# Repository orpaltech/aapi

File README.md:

ORPAL AA-PI
==============

Antenna analyzer project for portable Linux-based devices. 
The current hardware implementation is based on BananaPi M2-Magic SBC (Allwinner R16).

Version 4.3

Based on the Yuri Kuchura's EU1KY_AA_V3 https://github.com/EU1KY/eu1ky_aa_v3

Build
==============

The build process depends on the platform you have chosen. Currently the AA-PI software is managed by repository https://github.com/orpaltech/armlinux.

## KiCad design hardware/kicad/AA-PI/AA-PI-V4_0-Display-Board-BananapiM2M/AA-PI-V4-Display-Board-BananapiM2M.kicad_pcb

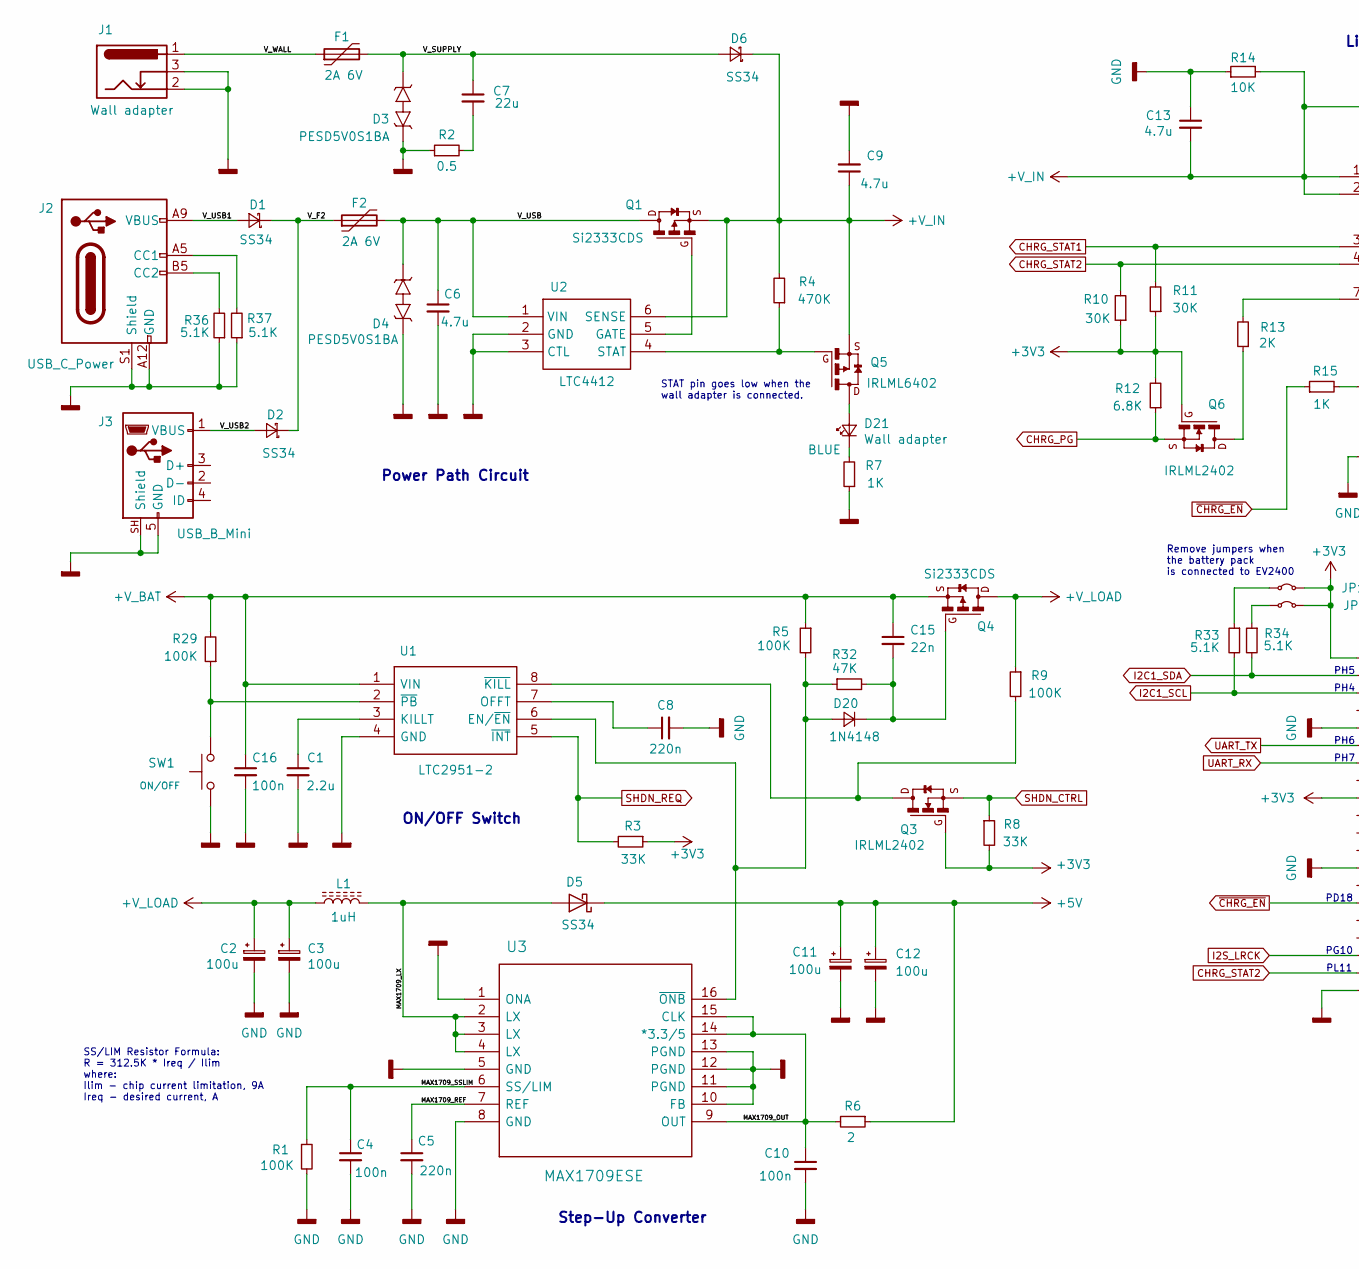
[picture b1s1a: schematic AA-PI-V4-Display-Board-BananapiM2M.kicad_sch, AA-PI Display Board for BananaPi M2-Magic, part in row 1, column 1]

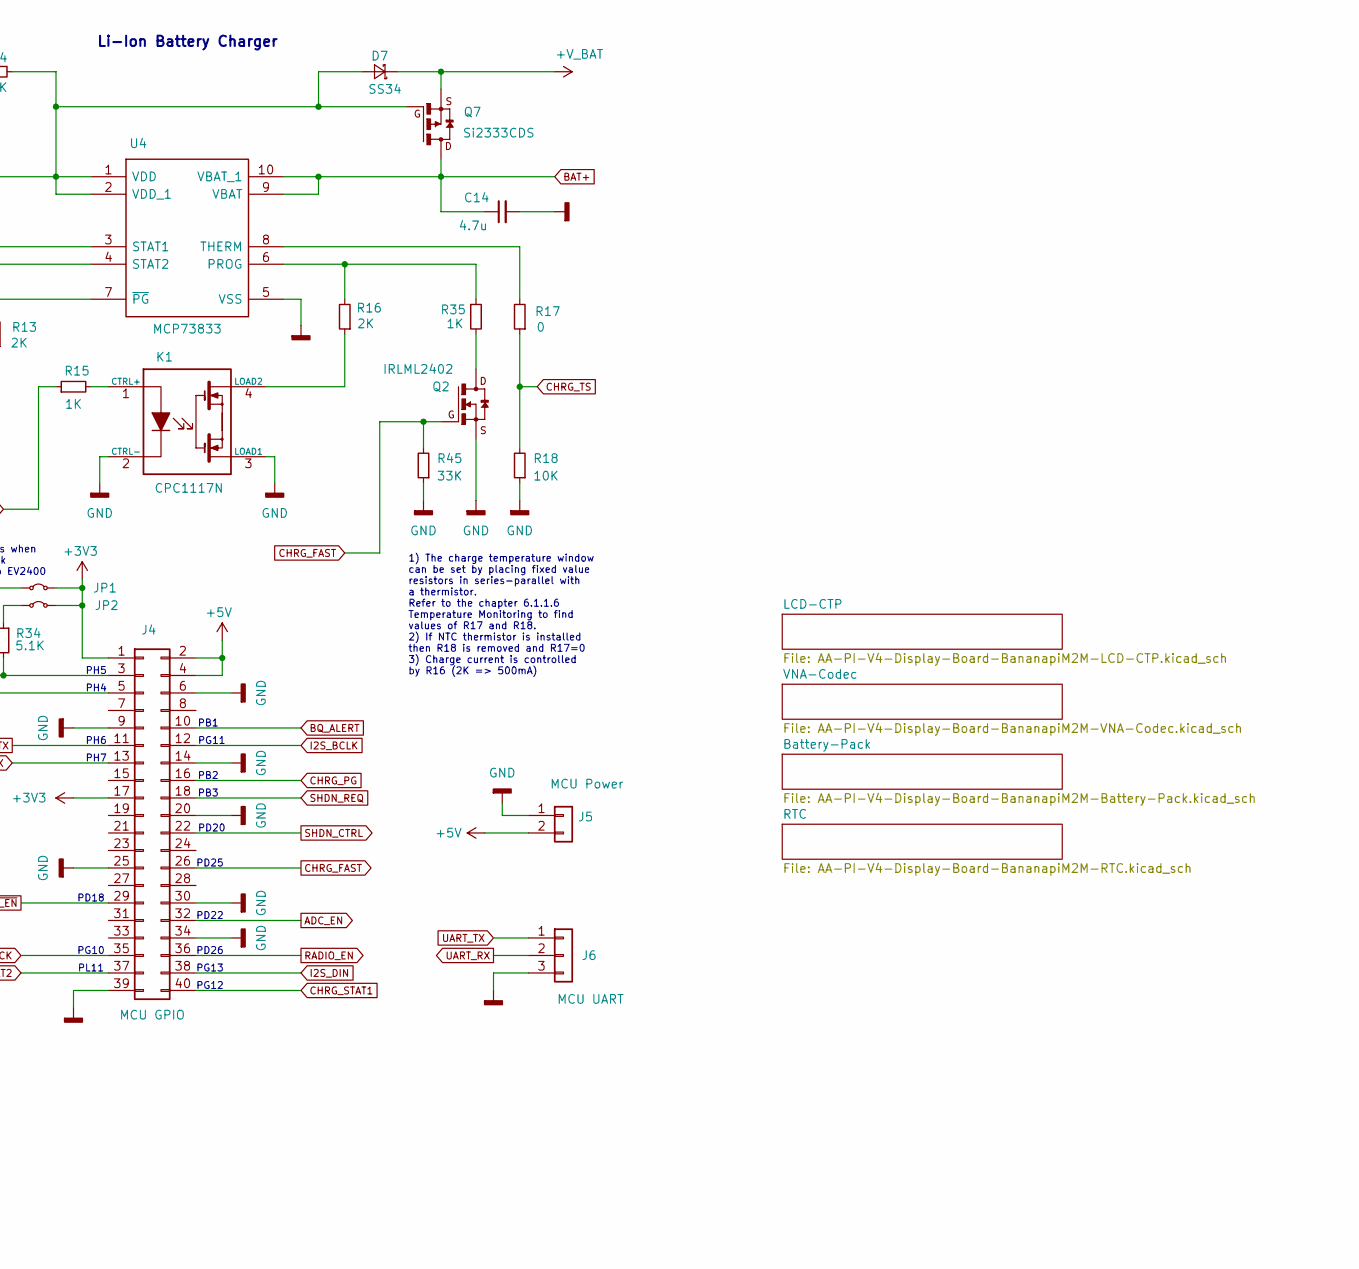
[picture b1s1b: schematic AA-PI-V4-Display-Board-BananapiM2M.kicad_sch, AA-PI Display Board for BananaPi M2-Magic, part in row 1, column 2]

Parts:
C1: 2.2u; C_0603_1608Metric
C2, C3, C11, C12: 100u; CP_EIA-7343-31_Kemet-D
C4, C10: 100n; C_1206_3216Metric
C5: 220n; C_1206_3216Metric
C6, C9, C13, C14: 4.7u; C_0805_2012Metric
C7: 22u; C_1206_3216Metric
C8: 220n; C_0603_1608Metric
C15: 22n; C_0603_1608Metric
C16: 100n; C_0603_1608Metric
D1, D2, D5, D6, D7: SS34; D_SMA
D3, D4: PESD5V0S1BA; D_SOD-323_HandSoldering
D20: 1N4148; D_SOD-323_HandSoldering
D21: Wall adapter; LED_0805_2012Metric_Pad1.15x1.40mm_HandSolder
F1, F2: 2A 6V; Fuse_1206_3216Metric_Pad1.42x1.75mm_HandSolder
J1: Wall adapter; DC-050-SMD-Power-Jack
J2: USB_C_Power; USB_C_Receptacle_GCT_USB4125-xx-x_6P_TopMnt_Horizontal
J3: USB_B_Mini; USB_Mini-B_Lumberg_2486_01_Horizontal
J4: MCU GPIO; PinSocket_2x20_P2.54mm_Vertical_SMD
J5: MCU Power; JST_PH_B2B-PH-SM4-TB_1x02-1MP_P2.00mm_Vertical
J6: MCU UART; PinHeader_1x03_P2.54mm_Vertical_SMD_Pin1Left
JP1, JP2: Jumper_2_Small_Bridged; PinHeader_2x01_P2.00mm_Vertical_SMD
K1: CPC1117N; SOP254P610X218-4N; Manufacturer_Part_Number CPC1117N
L1: 1uH; COILCRAFT_DO3316P102MLB
Q1, Q4, Q7: Si2333CDS; SOT-23
Q2, Q3, Q6: IRLML2402; SOT-23
Q5: IRLML6402; SOT-23
R1: 100K; R_1206_3216Metric
R2: 0.5; R_0805_2012Metric
R3, R8, R45: 33K; R_0603_1608Metric
R4: 470K; R_0805_2012Metric
R5, R9, R29: 100K; R_0603_1608Metric
R6: 2; R_1206_3216Metric
R7: 1K; R_0805_2012Metric
R10, R11: 30K; R_0603_1608Metric
R12: 6.8K; R_0603_1608Metric
R13, R16: 2K; R_0603_1608Metric
R14: 10K; R_0805_2012Metric
R15, R35: 1K; R_0603_1608Metric
R17: 0; R_0603_1608Metric
R18: 10K; R_0603_1608Metric
R32: 47K; R_0603_1608Metric
R33, R34: 5.1K; R_0603_1608Metric
R36, R37: 5.1K; R_0805_2012Metric
SW1: ON/OFF; SW_SPST_CK_RS282G05A3
U1: LTC2951-2; SOT65P280X100-8N; Manufacturer_Part_Number LTC2951CTS8-1#TRMPBF
U2: LTC4412; SOT95P280X100-6N; Manufacturer_Part_Number LTC4412ES6#TRMPBF
U3: MAX1709ESE; SOIC-16_3.9x9.9mm_P1.27mm
U4: MCP73833; SOP50P490X110-10N; Manufacturer_Part_Number MCP73833-FCI/UN

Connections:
+3V3: J4.1, J4.17, JP1.2 (B), JP2.2 (B), Q3.1 (G), Q6.1 (G), R3.1, R8.2, R10.1, R11.1, R12.2; also elsewhere on the board
+5V: C11.1, C12.1, D5.1 (K), J4.2, J4.4, J5.2, R6.1; also elsewhere on the board
+V_BAT: C15.1, C16.1, D7.1 (K), Q4.2 (S), Q7.2 (S), R5.1, R29.2, U1.1 (VIN)
+V_IN: C9.1, C13.2, D6.1 (K), D7.2 (A), Q1.2 (S), Q5.2 (S), Q7.1 (G), R4.2, R14.2, U2.6 (SENSE), U4.1 (VDD), U4.2 (VDD_1)
+V_LOAD: C2.1, C3.1, L1.1, Q4.3 (D), R9.1
/MAX1709_LX: D5.2 (A), L1.2, U3.2 (LX), U3.3 (LX), U3.4 (LX)
/MAX1709_OUT: C10.1, R6.2, U3.9 (OUT), U3.14 (*3.3/5), U3.15 (CLK)
/MAX1709_REF: C5.1, U3.7 (REF)
/MAX1709_SSLIM: C4.1, R1.1, U3.6 (SS/LIM)
/V_F2: D1.1 (K), D2.1 (K), F2.1
/V_SUPPLY: C7.1, D3.2, D6.2 (A), F1.2
/V_USB: C6.1, D4.2, F2.2, Q1.3 (D), U2.1 (VIN)
/V_USB1: D1.2 (A), J2.A9 (VBUS), J2.B9 (VBUS)
/V_USB2: D2.2 (A), J3.1 (VBUS)
/V_WALL: F1.1, J1.1
ADC_EN: J4.32; also elsewhere on the board
BAT+: C14.1, Q7.3 (D), U4.9 (VBAT), U4.10 (VBAT_1); also elsewhere on the board
BQ_ALERT: J4.10; also elsewhere on the board
CHRG_FAST: J4.26, Q2.1 (G), R45.2
CHRG_PG: J4.16, Q6.2 (S), R12.1
CHRG_STAT1: J4.40, R11.2, U4.3 (STAT1)
CHRG_STAT2: J4.37, R10.2, U4.4 (STAT2)
CHRG_TS: R17.1, R18.2; also elsewhere on the board
GND: C1.2, C2.2, C3.2, C4.2, C5.2, C6.2, C8.2, C9.2, C10.2, C11.2, C12.2, C13.1, C14.2, C16.2, D3.1, D4.1, J1.2, J1.3, J2.A12 (GND), J2.B12 (GND), J2.S1 (Shield), J3.5 (GND), J3.SH (Shield), J4.6, J4.9, J4.14, J4.20, J4.25, J4.30, J4.34, J4.39, J5.1, J6.3, K1.2 (CTRL-), K1.3 (LOAD1), Q2.2 (S), R1.2, R2.1, R7.1, R14.1, R18.1, R36.1, R37.1, R45.1, SW1.1, U1.4 (GND), U2.2 (GND), U2.3 (CTL), U3.1 (ONA), U3.5 (GND), U3.8 (GND), U3.10 (FB), U3.11 (PGND), U3.12 (PGND), U3.13 (PGND), U4.5 (VSS); also elsewhere on the board
I2C1_SCL: J4.5, R33.2; also elsewhere on the board
I2C1_SDA: J4.3, R34.2; also elsewhere on the board
I2S_BCLK: J4.12; also elsewhere on the board
I2S_DIN: J4.38; also elsewhere on the board
I2S_LRCK: J4.35; also elsewhere on the board
unnamed: C7.2, R2.2
unnamed: D20.2 (A), R5.2, R32.1, U1.6 (EN/~EN), U3.16 (~ONB)
unnamed: C15.2, D20.1 (K), Q4.1 (G), R32.2
unnamed: D21.2 (A), Q5.3 (D)
unnamed: D21.1 (K), R7.2
unnamed: J2.A5 (CC1), R37.2
unnamed: J2.B5 (CC2), R36.2
unnamed: JP1.1 (A), R33.1
unnamed: JP2.1 (A), R34.1
unnamed: K1.1 (CTRL+), R15.2
unnamed: K1.4 (LOAD2), R16.1
unnamed: Q1.1 (G), U2.5 (GATE)
unnamed: Q2.3 (D), R35.2
unnamed: Q3.3 (D), R9.2, U1.8 (~KILL)
unnamed: Q5.1 (G), R4.1, U2.4 (STAT)
unnamed: Q6.3 (D), R13.1
unnamed: C1.1, U1.3 (KILLT)
unnamed: C8.1, U1.7 (OFFT)
unnamed: R29.1, SW1.2, U1.2 (~PB)
unnamed: R16.2, R35.1, U4.6 (PROG)
unnamed: R17.2, U4.8 (THERM)
unnamed: R13.2, U4.7 (~PG)
RADIO_EN: J4.36; also elsewhere on the board
SHDN_CTRL: J4.22, Q3.2 (S), R8.1
SHDN_REQ: J4.18, R3.2, U1.5 (~INT)
UART_RX: J4.13, J6.2
UART_TX: J4.11, J6.1
~CHRG_EN: J4.29, R15.1

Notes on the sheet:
PH4
PD26
SS/LIM Resistor Formula: R = 312.5K * Ireq / Ilim where: Ilim - chip current limitation, 9A Ireq - desired current, A
STAT pin goes low when the wall adapter is connected.
PD20
PG12
PG10
PB1
PB3
Power Path Circuit
1) The charge temperature window can be set by placing fixed value resistors in series-parallel with a thermistor. Refer to the chapter 6.1.1.6 Temperature Monitoring to find values of R17 and R18. 2) If NTC thermistor is installed then R18 is removed and R17=0 3) Charge current is controlled by R1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
PG11
Step-Up Converter
PH6
ON/OFF Switch
PH7
PB2
Remove jumpers when the battery pack is connected to EV2400
PD18
PG13
PD25
PH5
PD22
Li-Ion Battery Charger
PL11

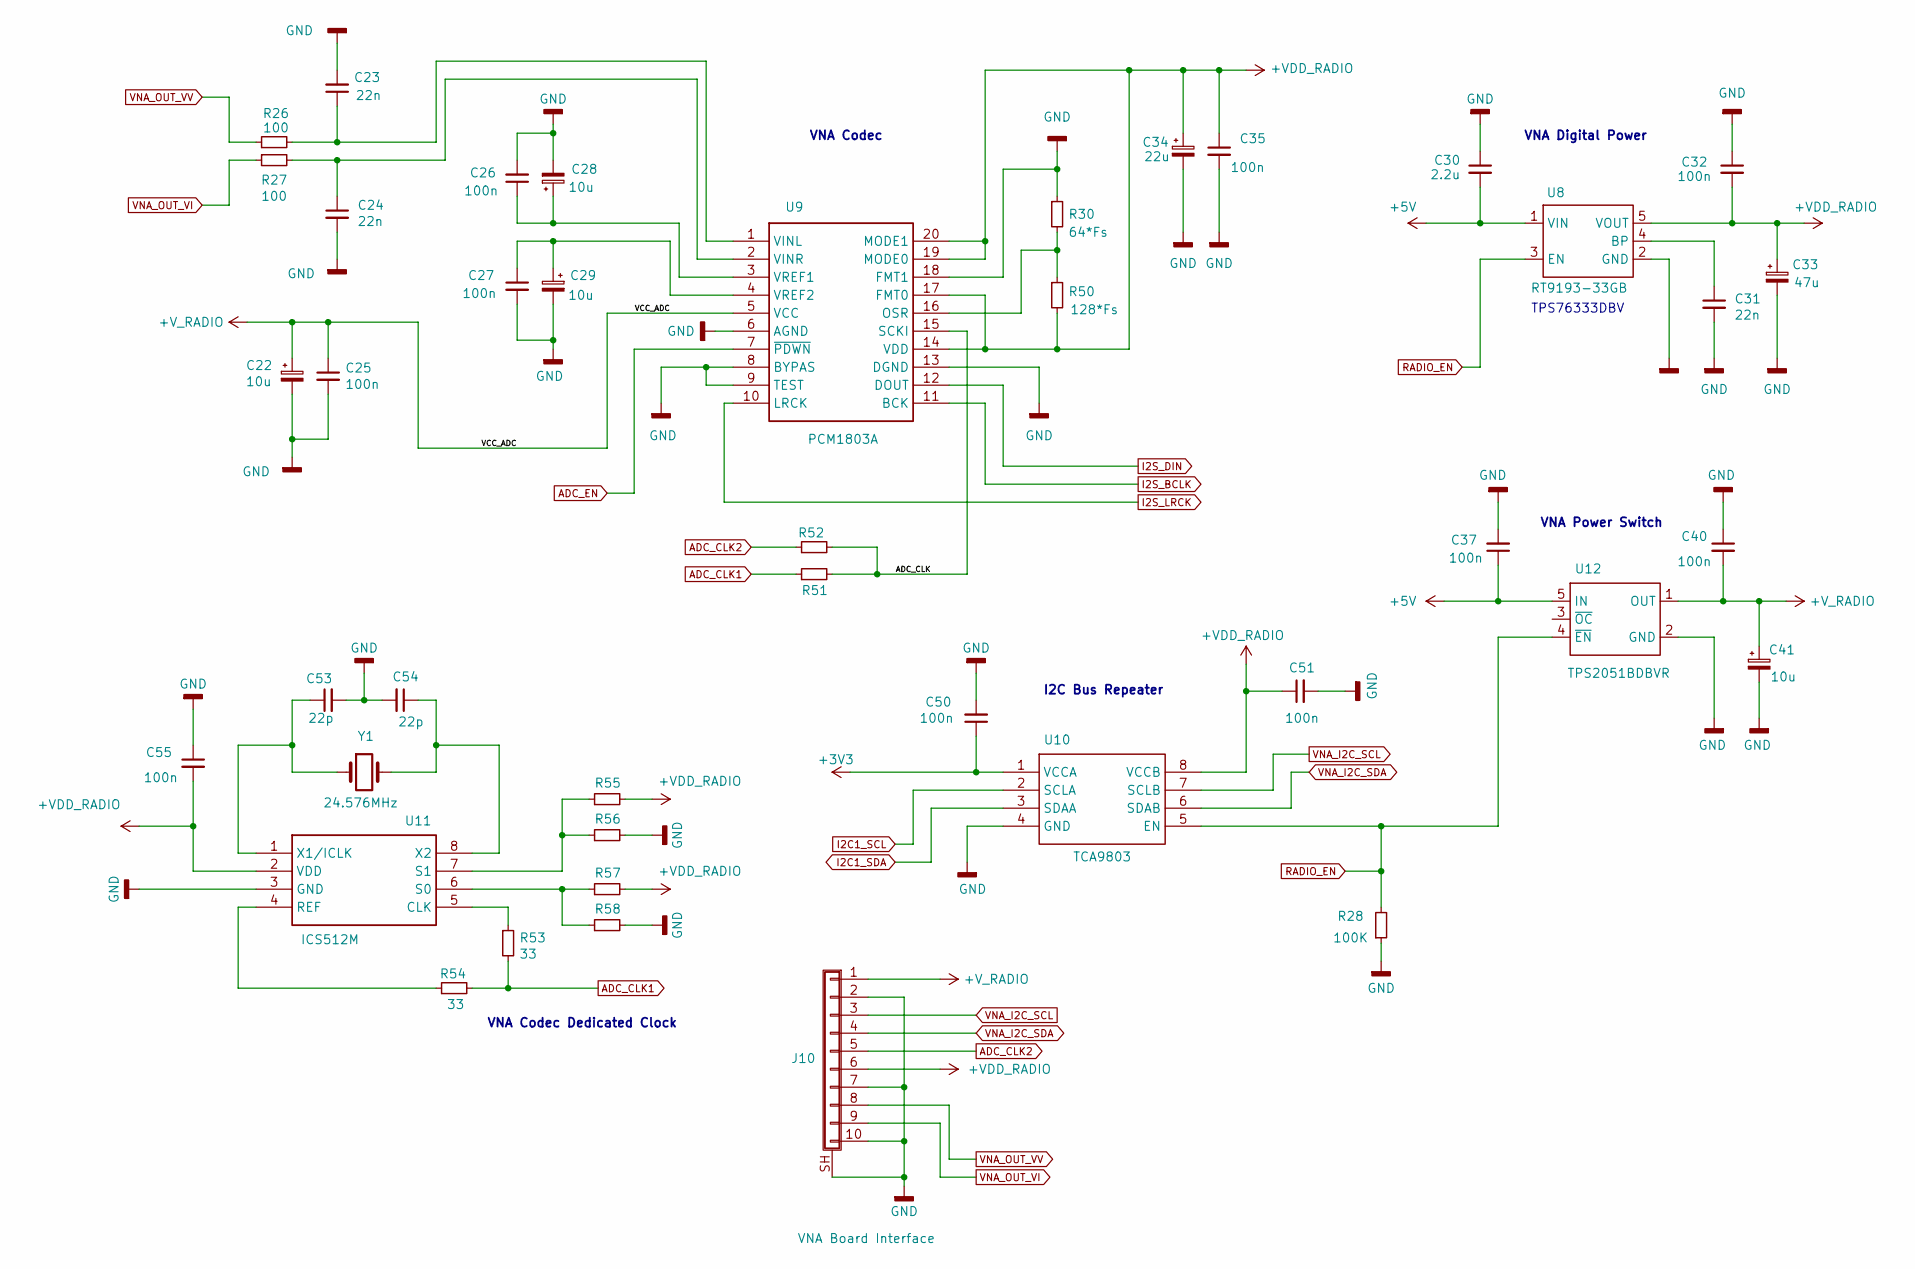
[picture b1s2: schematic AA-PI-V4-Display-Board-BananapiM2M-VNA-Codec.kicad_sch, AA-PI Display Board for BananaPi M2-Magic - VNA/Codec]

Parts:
C22, C28, C29: 10u; CP_EIA-3216-18_Kemet-A
C23, C24: 22n; C_0603_1608Metric
C25, C26, C27, C35, C50, C51, C55: 100n; C_0603_1608Metric
C30: 2.2u; C_0805_2012Metric_Pad1.15x1.40mm_HandSolder
C31: 22n; C_0805_2012Metric
C32, C37, C40: 100n; C_0805_2012Metric
C33: 47u; CP_EIA-3528-21_Kemet-B
C34: 22u; CP_EIA-3216-18_Kemet-A
C41: 10u; CP_EIA-3528-21_Kemet-B
C53, C54: 22p; C_0603_1608Metric
J10: VNA Board Interface; 1.25-AB-SMT-10pin-Vertical
R26, R27: 100; R_0603_1608Metric
R28: 100K; R_0603_1608Metric
R30: 64*Fs; R_0603_1608Metric
R50: 128*Fs; R_0603_1608Metric
R51, R52, R55, R56, R57, R58: 0; R_0603_1608Metric
R53, R54: 33; R_0603_1608Metric
U8: RT9193-33GB; SOT94P279X130-5N; Manufacturer_Part_Number RT9193
U9: PCM1803A; SOP65P780X200-20N; Manufacturer_Part_Number PCM1803DBR; Mouser Part Number 595-PCM1803DBR
U10: TCA9803; SOP65P490X110-8N; Manufacturer_Part_Number TCA9802DGKR
U11: ICS512M; SOIC127P600X175-8N; Manufacturer_Part_Number ICS512MILF
U12: TPS2051BDBVR; SOT95P280X145-5N; Manufacturer_Part_Number TPS2051BDBVR
Y1: 24.576MHz; Crystal_SMD_5032-2Pin_5.0x3.2mm

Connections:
+3V3: C50.1, U10.1 (VCCA); also elsewhere on the board
+5V: C30.2, C37.1, U8.1 (VIN), U12.5 (IN); also elsewhere on the board
+VDD_RADIO: C32.2, C33.1, C34.1, C35.1, C51.1, C55.2, J10.6, R50.2, R55.2, R57.2, U8.5 (VOUT), U9.14 (VDD), U9.17 (FMT0), U9.19 (MODE0), U9.20 (MODE1), U10.8 (VCCB), U11.2 (VDD)
+V_RADIO: C22.1, C25.1, C40.2, C41.1, J10.1, U9.5 (VCC), U12.1 (OUT)
/VNA-Codec/ADC_CLK: R51.2, R52.2, U9.15 (SCKI)
ADC_CLK1: R51.1, R53.2, R54.2
ADC_CLK2: J10.5, R52.1
ADC_EN: U9.7 (~PDWN); also elsewhere on the board
GND: C22.2, C23.2, C24.2, C25.2, C26.2, C27.2, C28.2, C29.2, C30.1, C31.2, C32.1, C33.2, C34.2, C35.2, C37.2, C40.1, C41.2, C50.2, C51.2, C53.2, C54.2, C55.1, J10.2, J10.7, J10.10, J10.SH (Shield), R28.1, R30.1, R56.2, R58.2, U8.2 (GND), U9.6 (AGND), U9.8 (BYPAS), U9.9 (TEST), U9.13 (DGND), U9.18 (FMT1), U10.4 (GND), U11.3 (GND), U12.2 (GND); also elsewhere on the board
I2C1_SCL: U10.2 (SCLA); also elsewhere on the board
I2C1_SDA: U10.3 (SDAA); also elsewhere on the board
I2S_BCLK: U9.11 (BCK); also elsewhere on the board
I2S_DIN: U9.12 (DOUT); also elsewhere on the board
I2S_LRCK: U9.10 (LRCK); also elsewhere on the board
unnamed: C31.1, U8.4 (BP)
unnamed: R30.2, R50.1, U9.16 (OSR)
unnamed: C23.1, R26.2, U9.1 (VINL)
unnamed: C24.1, R27.2, U9.2 (VINR)
unnamed: C26.1, C28.1, U9.3 (VREF1)
unnamed: C27.1, C29.1, U9.4 (VREF2)
unnamed: R53.1, U11.5 (CLK)
unnamed: R54.1, U11.4 (REF)
unnamed: R57.1, R58.1, U11.6 (S0)
unnamed: R55.1, R56.1, U11.7 (S1)
unnamed: C53.1, U11.1 (X1/ICLK), Y1.1
unnamed: C54.1, U11.8 (X2), Y1.2
RADIO_EN: R28.2, U8.3 (EN), U10.5 (EN), U12.4 (~EN); also elsewhere on the board
VNA_I2C_SCL: J10.3, U10.7 (SCLB)
VNA_I2C_SDA: J10.4, U10.6 (SDAB)
VNA_OUT_VI: J10.9, R27.1
VNA_OUT_VV: J10.8, R26.1

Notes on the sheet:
VNA Power Switch
VNA Codec
VNA Codec Dedicated Clock
I2C Bus Repeater
TPS76333DBV
VNA Digital Power

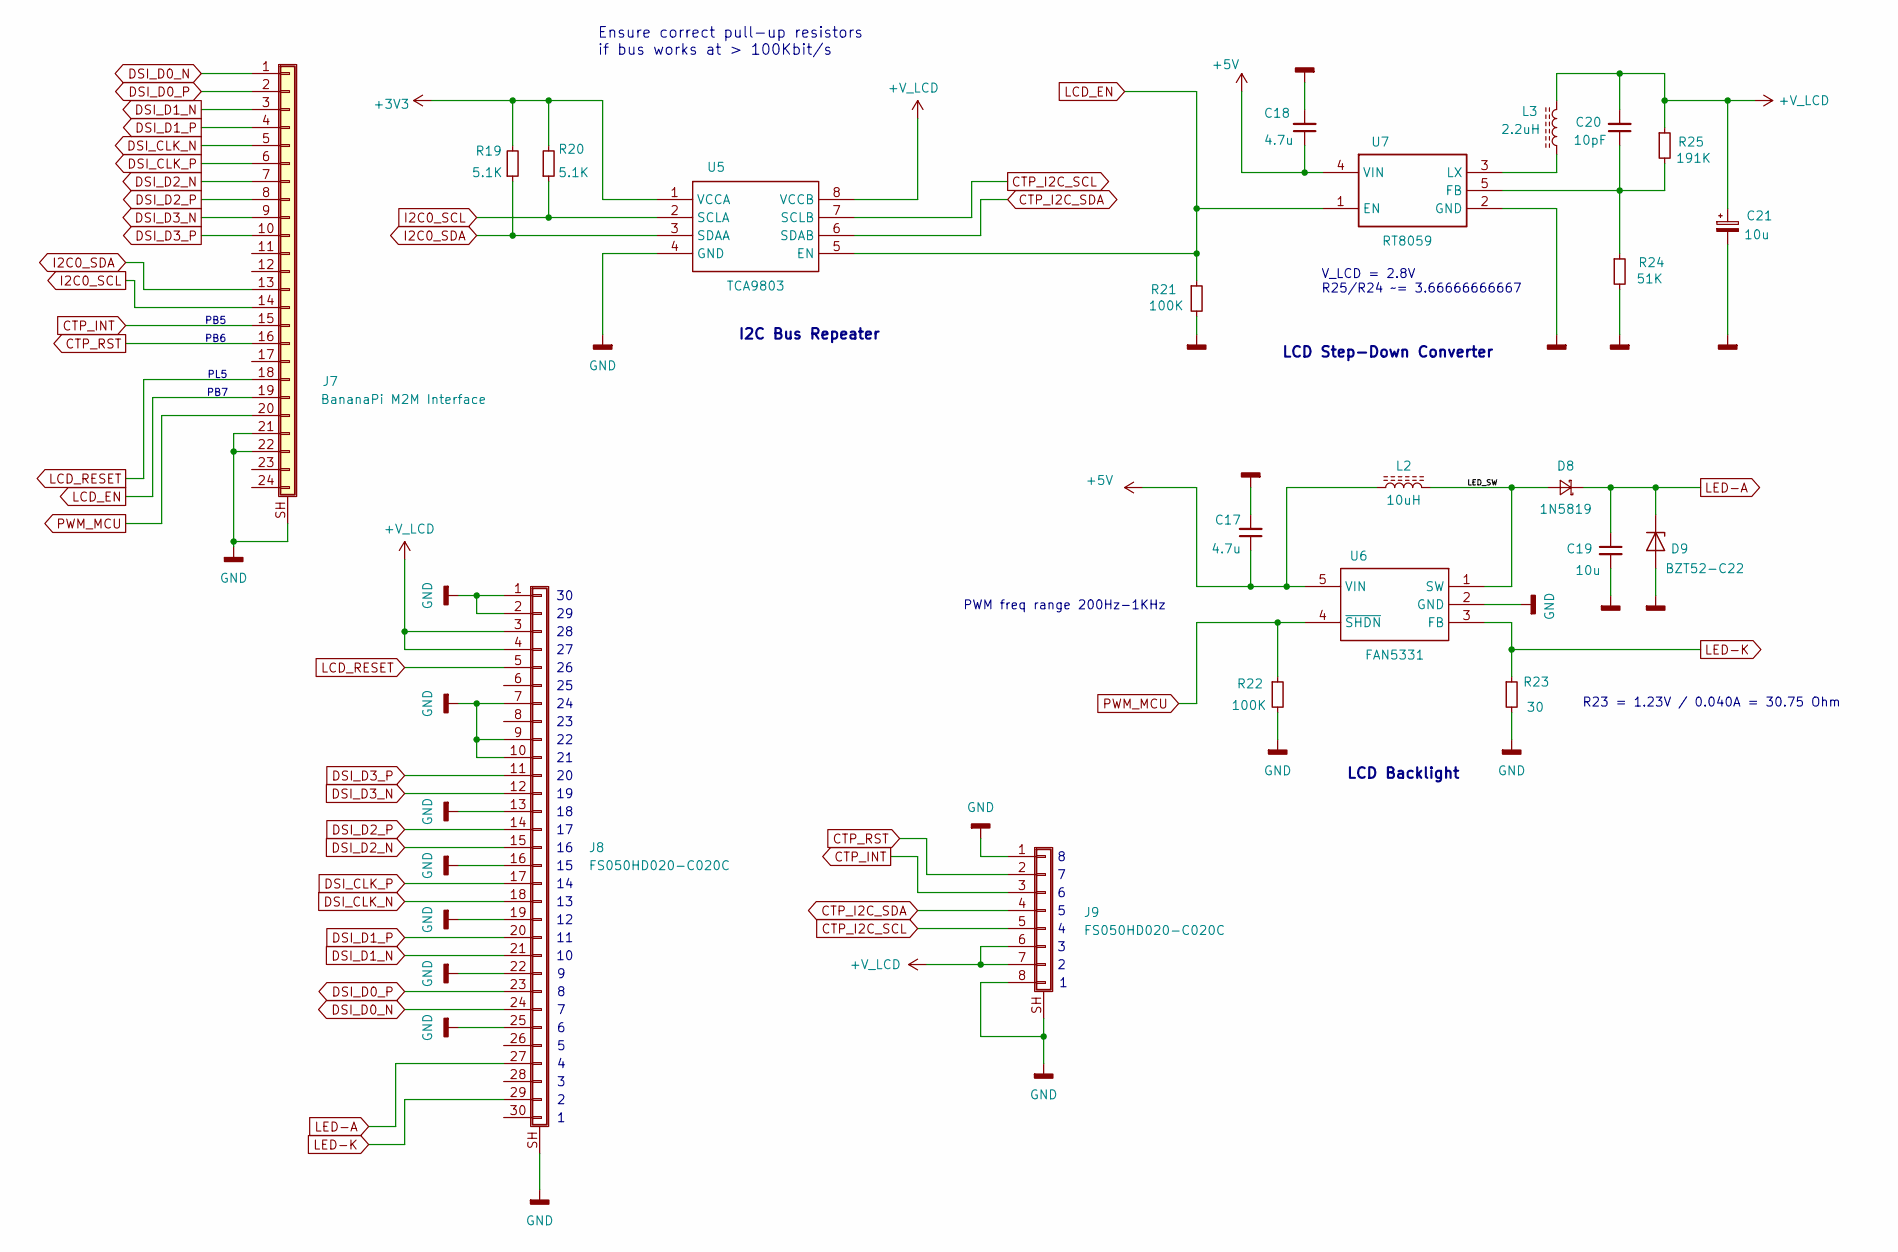
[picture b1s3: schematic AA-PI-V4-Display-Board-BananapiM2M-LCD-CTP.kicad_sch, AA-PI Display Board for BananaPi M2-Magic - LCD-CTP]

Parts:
C17, C18: 4.7u; C_0805_2012Metric
C19: 10u; C_0805_2012Metric
C20: 10pF; C_0805_2012Metric
C21: 10u; CP_EIA-3528-21_Kemet-B
D8: 1N5819; D_SOD-123
D9: BZT52-C22; D_SOD-123
J7: BananaPi M2M Interface; FPC-0.5-1-24P_CLAMSH_BTM
J8: FS050HD020-C020C; FPC-0.5-1-30P_Clamshell_Bottom
J9: FS050HD020-C020C; FPC-0.5-1-8P_Clamshell_Bottom
L2: 10uH; COILCRAFT_XEL5050_HandSolder
L3: 2.2uH; COILCRAFT_XEL5050_HandSolder
R19, R20: 5.1K; R_0603_1608Metric
R21, R22: 100K; R_0603_1608Metric
R23: 30; R_0805_2012Metric
R24: 51K; R_0603_1608Metric
R25: 191K; R_0603_1608Metric
U5: TCA9803; SOP65P490X110-8N; Manufacturer_Part_Number TCA9802DGKR
U6: FAN5331; SOT95P270X145-5N; Manufacturer_Part_Number FAN5333BSX
U7: RT8059; SOT94P280X100-5N; Manufacturer_Part_Number RT8059GJ5; Mouser Part Number 835-RT8059GJ5

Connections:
+3V3: R19.2, R20.2, U5.1 (VCCA); also elsewhere on the board
+5V: C17.1, C18.1, L2.1, U6.5 (VIN), U7.4 (VIN); also elsewhere on the board
+V_LCD: C20.2, C21.1, J8.3, J8.4, J9.6, J9.7, L3.2, R25.1, U5.8 (VCCB)
/LCD-CTP/LED_SW: D8.2 (A), L2.2, U6.1 (SW)
CTP_I2C_SCL: J9.5, U5.7 (SCLB)
CTP_I2C_SDA: J9.4, U5.6 (SDAB)
CTP_INT: J7.15, J9.3
CTP_RST: J7.16, J9.2
DSI_CLK_N: J7.5, J8.18
DSI_CLK_P: J7.6, J8.17
DSI_D0_N: J7.1, J8.24
DSI_D0_P: J7.2, J8.23
DSI_D1_N: J7.3, J8.21
DSI_D1_P: J7.4, J8.20
DSI_D2_N: J7.7, J8.15
DSI_D2_P: J7.8, J8.14
DSI_D3_N: J7.9, J8.12
DSI_D3_P: J7.10, J8.11
GND: C17.2, C18.2, C19.2, C21.2, D9.2 (A), J7.21, J7.22, J7.SH (Shield), J8.1, J8.2, J8.7, J8.9, J8.10, J8.13, J8.16, J8.19, J8.22, J8.25, J8.SH (Shield), J9.1, J9.8, J9.SH (Shield), R21.2, R22.2, R23.2, R24.2, U5.4 (GND), U6.2 (GND), U7.2 (GND); also elsewhere on the board
I2C0_SCL: J7.14, R20.1, U5.2 (SCLA)
I2C0_SDA: J7.13, R19.1, U5.3 (SDAA)
LCD_EN: J7.19, R21.1, U5.5 (EN), U7.1 (EN)
LCD_RESET: J7.18, J8.5
LED-A: C19.1, D8.1 (K), D9.1 (K), J8.27
LED-K: J8.29, R23.1, U6.3 (FB)
unnamed: C20.1, R24.1, R25.2, U7.5 (FB)
unnamed: L3.1, U7.3 (LX)
PWM_MCU: J7.20, R22.1, U6.4 (~SHDN)

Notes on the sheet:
PB7
R23 = 1.23V / 0.040A = 30.75 Ohm
PB6
LCD Step-Down Converter
PWM freq range 200Hz-1KHz
I2C Bus Repeater
LCD Backlight
PB5
PL5
V_LCD = 2.8V R25/R24 ~= 3.66666666667
Ensure correct pull-up resistors if bus works at > 100Kbit/s

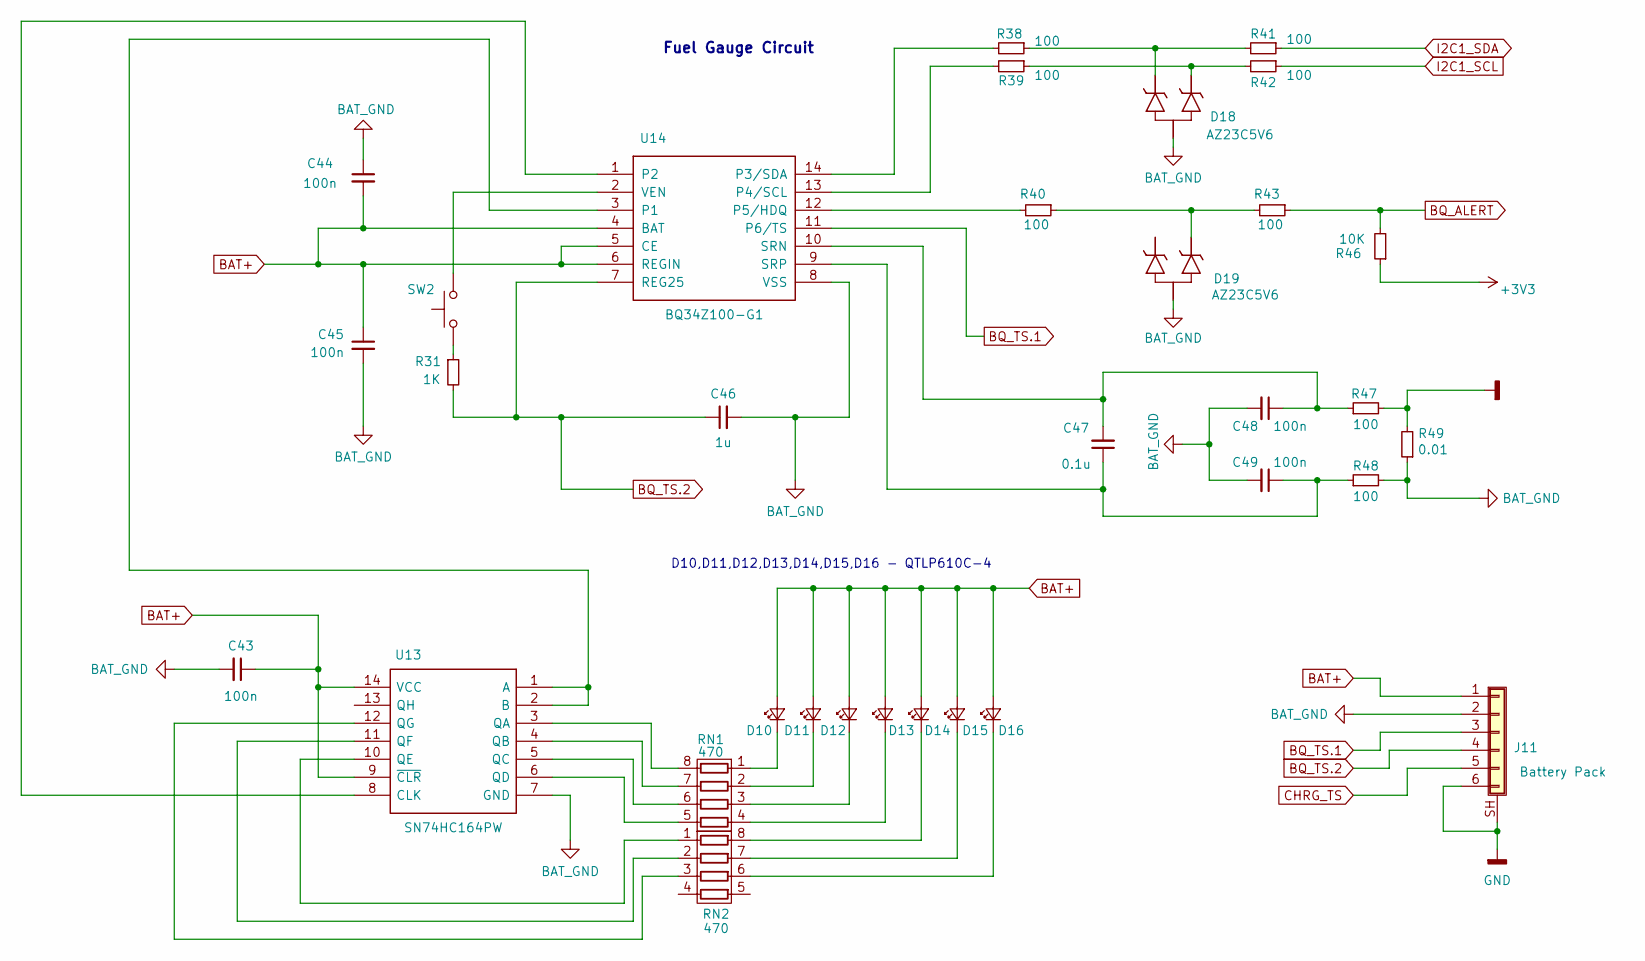
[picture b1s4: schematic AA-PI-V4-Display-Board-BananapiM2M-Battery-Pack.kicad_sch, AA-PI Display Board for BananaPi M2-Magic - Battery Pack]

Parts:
C43, C44, C45, C48, C49: 100n; C_0603_1608Metric
C46: 1u; C_0805_2012Metric_Pad1.15x1.40mm_HandSolder
C47: 0.1u; C_0603_1608Metric
D10, D11, D12, D13, D14, D15, D16: QTLP610C-4; QTLP610C4TR_2; Manufacturer_Part_Number QTLP610C4TR
D18, D19: AZ23C5V6; SOT96P240X110-3N; Manufacturer_Part_Number AZ23C2V7-AZ23C51
J11: Battery Pack; JST_PH_B6B-PH-SM4-TB_1x06-1MP_P2.00mm_Vertical
R31: 1K; R_0603_1608Metric
R38, R39, R40, R41, R42, R43, R47, R48: 100; R_0603_1608Metric
R46: 10K; R_0603_1608Metric
R49: 0.01; R_0805_2012Metric
RN1, RN2: 470; R_Array_Convex_4x0603
SW2: SW_Push; SW_SPST_3X4X2.5_SMD
U13: SN74HC164PW; SOP65P640X120-14N; Manufacturer_Part_Number SN74HC164PW
U14: BQ34Z100-G1; SOP65P640X120-14N; Manufacturer_Part_Number BQ34Z100PWR-G1

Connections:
+3V3: R46.1; also elsewhere on the board
BAT+: C43.1, C44.2, C45.1, D10.2 (A), D11.2 (A), D12.2 (A), D13.2 (A), D14.2 (A), D15.2 (A), D16.2 (A), J11.1, U13.9 (~CLR), U13.14 (VCC), U14.4 (BAT), U14.5 (CE), U14.6 (REGIN); also elsewhere on the board
BAT_GND: C43.2, C44.1, C45.2, C46.2, C48.2, C49.2, D18.3, D19.3, J11.2, R48.2, R49.1, U13.7 (GND), U14.8 (VSS)
BQ_ALERT: R43.1, R46.2; also elsewhere on the board
BQ_TS.1: J11.3, U14.11 (P6/TS)
BQ_TS.2: C46.1, J11.4, R31.2, U14.7 (REG25)
CHRG_TS: J11.5; also elsewhere on the board
GND: J11.6, J11.SH (Shield), R47.2, R49.2; also elsewhere on the board
I2C1_SCL: R42.1; also elsewhere on the board
I2C1_SDA: R41.1; also elsewhere on the board
unnamed: D10.1 (K), RN1.1 (R1.1)
unnamed: D11.1 (K), RN1.2 (R2.1)
unnamed: D12.1 (K), RN1.3 (R3.1)
unnamed: D13.1 (K), RN1.4 (R4.1)
unnamed: D14.1 (K), RN2.8 (R1.2)
unnamed: D15.1 (K), RN2.7 (R2.2)
unnamed: D16.1 (K), RN2.6 (R3.2)
unnamed: D18.1, R39.1, R42.2
unnamed: D18.2, R38.1, R41.2
unnamed: D19.1, R40.1, R43.2
unnamed: R31.1, SW2.1
unnamed: RN1.8 (R1.2), U13.3 (QA)
unnamed: RN1.7 (R2.2), U13.4 (QB)
unnamed: RN1.6 (R3.2), U13.5 (QC)
unnamed: RN1.5 (R4.2), U13.6 (QD)
unnamed: RN2.1 (R1.1), U13.10 (QE)
unnamed: RN2.2 (R2.1), U13.11 (QF)
unnamed: RN2.3 (R3.1), U13.12 (QG)
unnamed: U13.1 (A), U13.2 (B), U14.3 (P1)
unnamed: U13.8 (CLK), U14.1 (P2)
unnamed: R38.2, U14.14 (P3/SDA)
unnamed: R39.2, U14.13 (P4/SCL)
unnamed: R40.2, U14.12 (P5/HDQ)
unnamed: C47.2, C48.1, R47.1, U14.10 (SRN)
unnamed: C47.1, C49.1, R48.1, U14.9 (SRP)
unnamed: SW2.2, U14.2 (VEN)

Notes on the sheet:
D10,D11,D12,D13,D14,D15,D16 - QTLP610C-4
Fuel Gauge Circuit

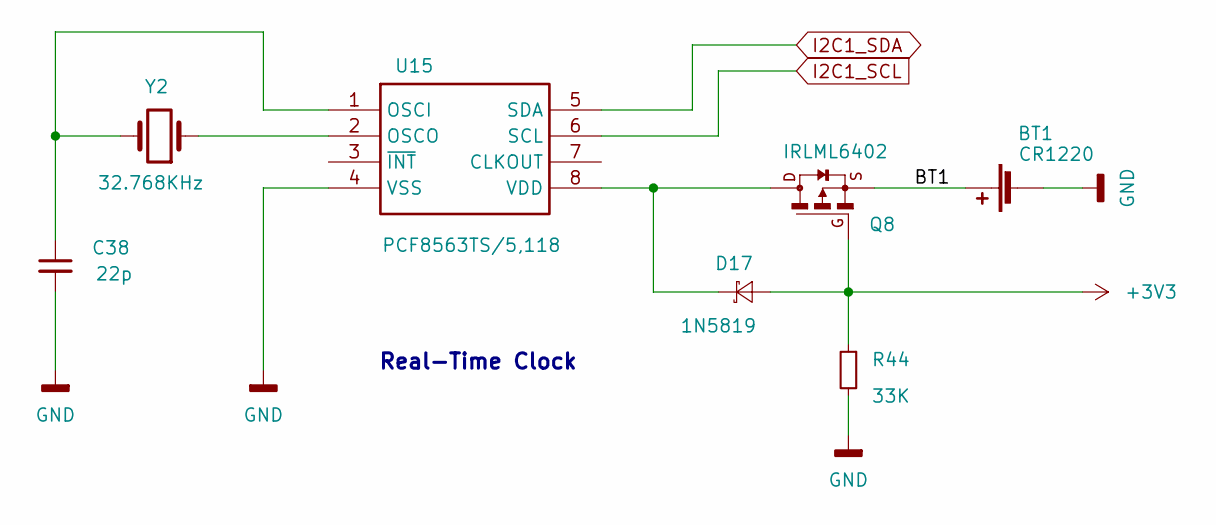
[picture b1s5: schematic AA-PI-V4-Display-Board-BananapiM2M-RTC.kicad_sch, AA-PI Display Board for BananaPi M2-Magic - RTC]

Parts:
BT1: CR1220; CR1220-2
C38: 22p; C_0603_1608Metric
D17: 1N5819; D_SOD-323_HandSoldering
Q8: IRLML6402; SOT-23
R44: 33K; R_0603_1608Metric
U15: PCF8563TS/5,118; SOT65P490X110-8N; Manufacturer_Part_Number PCF8563TS/5,118; Mouser Part Number 771-PCF8563TS/5118
Y2: 32.768KHz; Crystal_SMD_3215-2Pin_3.2x1.5mm

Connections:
+3V3: D17.2 (A), Q8.1 (G), R44.1; also elsewhere on the board
/RTC/BT1: BT1.1 (+), Q8.2 (S)
GND: BT1.2 (-), C38.2, R44.2, U15.4 (VSS); also elsewhere on the board
I2C1_SCL: U15.6 (SCL); also elsewhere on the board
I2C1_SDA: U15.5 (SDA); also elsewhere on the board
unnamed: D17.1 (K), Q8.3 (D), U15.8 (VDD)
unnamed: C38.1, U15.1 (OSCI), Y2.2
unnamed: U15.2 (OSCO), Y2.1

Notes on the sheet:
Real-Time Clock

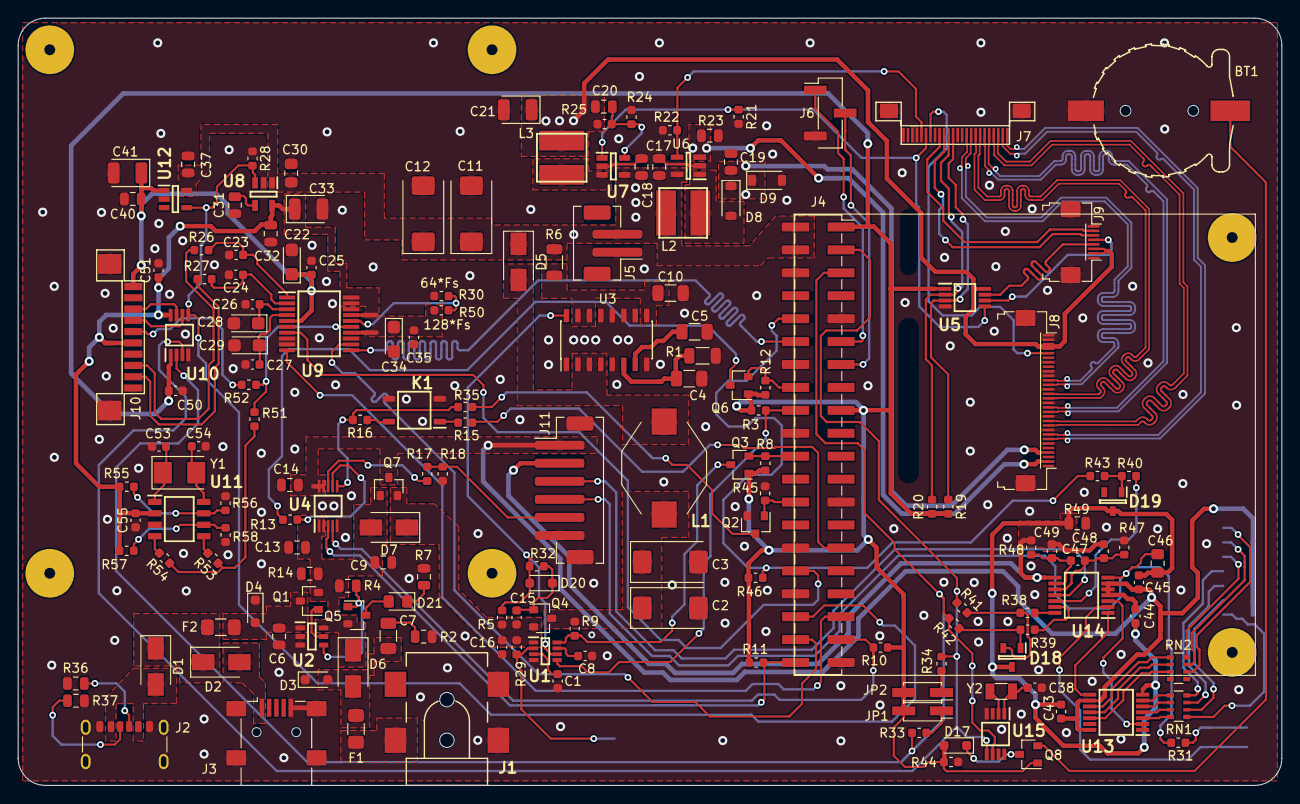
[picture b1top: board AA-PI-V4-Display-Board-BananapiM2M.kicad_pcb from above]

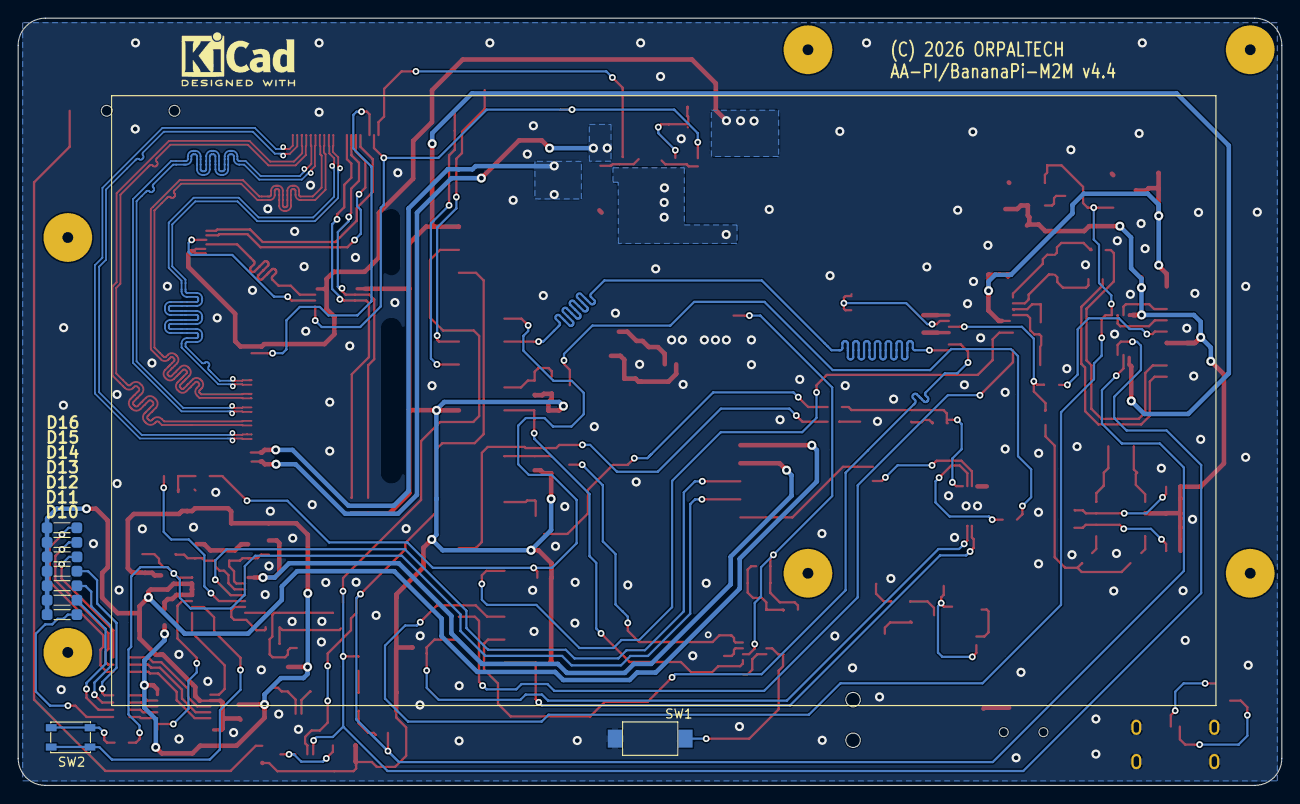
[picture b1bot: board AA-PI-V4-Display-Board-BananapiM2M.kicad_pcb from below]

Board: 2 copper layers, 140.0 x 85.0 mm, 186 parts (9 on the bottom side), 136 nets.

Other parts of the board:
CH1: CTP-CABLE-HOLE
SS2, SS4, SS5, SS6, SS7, SS8: PCB-Standoff-Spacer-SMD-M3

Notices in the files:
hardware/kicad/AA-PI-V2_2-Display-Board-NanoPiA64/AA-PI-V2_2-Display-Board-NanoPiA64.kicad_pcb:
(C) 2013-2019 ORPALTECH
hardware/kicad/EV2400/EV2400-EVM-Interface-Board/EV2400-EVM-Interface-Board.kicad_pcb:
(C) 2024
